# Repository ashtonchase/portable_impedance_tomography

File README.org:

* Portable Impedance Tomography System
This repository supports the UAH CPE 621 Advanced Embedded Systems project centered around the [[http://www.analog.com/media/en/technical-documentation/data-sheets/AD5933.pdf][Analog Devices AD5933 Impedance Analyzer]] for the use of impedance tomography.

** Overview

TBD

** Repository Structure

TBD

** Software 

Drivers are included for controlling the AD5933 module. Communication with the module is performed over I2C. The software drivers are device independent, so specific functions are to be used to map driver functionality to specific peripherals.

*** Porting Guide

A software porting guide is provided in [[./software/ad5933/hal/PORTING.org][PORTING GUIDLINE]]. 

** PCB Design 

A custom printed circuit board design is included. The design was developed in [[http://www.kicad.com][Kicad]].  The PCB project is available here [[https://github.com/ashtonchase/portable_impedance_tomography/tree/master/hardware/kicad_project][here]]. 

This PCB design in available via OSH Park. The project is located [[https://oshpark.com/shared_projects/npJ3mGp4][here]]

[[./hardware/kicad_project/output/top.png]]

[[./hardware/kicad_project/output/bottom.png]]

[[./hardware/kicad_project/output/3dtop.png]]

[[./hardware/kicad_project/output/3dbottom.png]]

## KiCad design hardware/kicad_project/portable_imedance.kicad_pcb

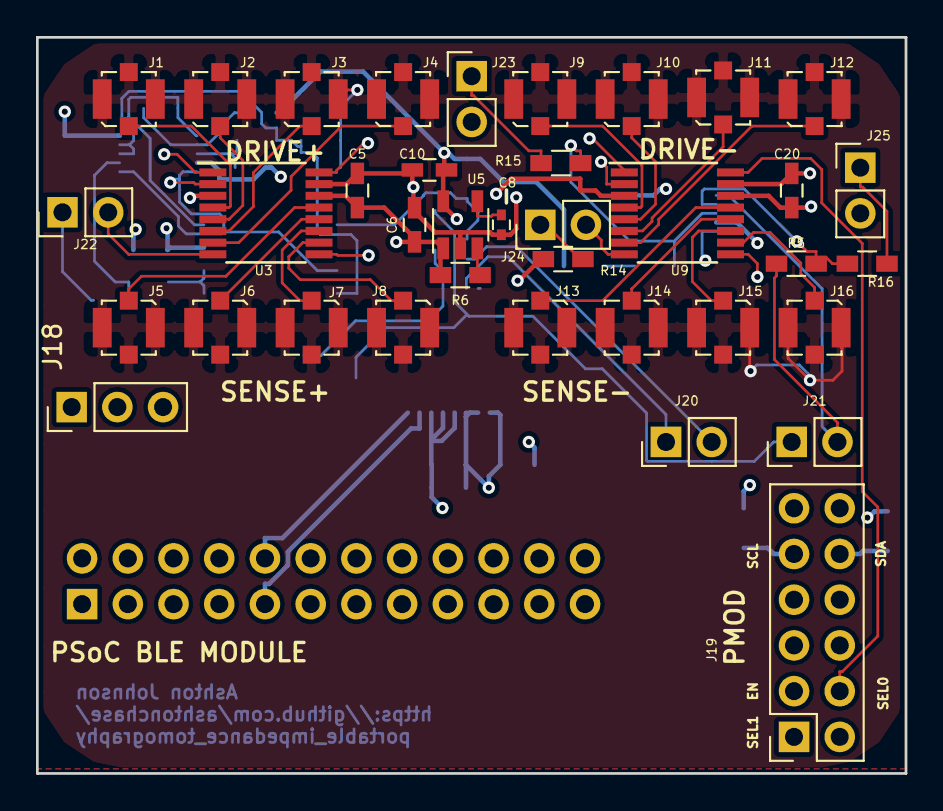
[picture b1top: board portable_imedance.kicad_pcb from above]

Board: 4 copper layers, 48.3 x 40.9 mm, 63 parts (0 on the bottom side), 51 nets.

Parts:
C1, C2: 0.1uF; C_0603_HandSoldering
C3: 10uF; C_0603_HandSoldering
C5, C20: 0.1u; C_0603_HandSoldering
C6, C10, C15, C16: 1u; C_0603_HandSoldering
C8: 10n; C_0402
C13: 33n; C_0402
C14, C18: 100n; C_0603_HandSoldering
J1, J2, J3, J4, J5, J6, J7, J8, J9, J10, J11, J12, J13, J14, J15, J16: UMC; Molex_Microcoaxial_RF
J17: Conn_02x12_Odd_Even; Socket_Strip_Straight_2x12_Pitch2.54mm
J18: Conn_01x03; Socket_Strip_Straight_1x03_Pitch2.54mm
J19: Conn_02x06_Odd_Even; Socket_Strip_Straight_2x06_Pitch2.54mm
J20, J21, J22, J23, J24, J25: Conn_01x02; Socket_Strip_Straight_1x02_Pitch2.54mm
R1, R2: 4.7k; R_0603_HandSoldering
R3, R5, R6, R10, R15, R16: 1k; R_0603_HandSoldering
R4, R13, R14, R17: 0; R_0603_HandSoldering
R7: 75k; R_0603_HandSoldering
R8, R9: 1M; R_0603_HandSoldering
R11: 75; R_0603_HandSoldering
R12: 10k; R_0603_HandSoldering
RV1: 20K; Potentiometer_Trimmer_Bourns_3214W
U2: AD5933; SSOP-16_5.3x6.2mm_Pitch0.65mm
U3, U9: ADG1209; TSSOP-16_4.4x5mm_Pitch0.65mm
U5: LD3985G25R_TSOT23; TSOT-23-5
U6, U7: OPA2836; TSSOP-10_3x3mm_Pitch0.5mm
U8: AD8130; SO-8_5.3x6.2mm_Pitch1.27mm

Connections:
+2V5: C10.1, R7.1, R9.1, R14.2, R17.2, U5.5
/AD5933 Front End/DRIVE_N: J24.1, R14.1
/AD5933 Front End/DRIVE_P: J22.1, R13.1
/AD5933 Front End/EN: J17.4, J19.3, U3.2, U6.5, U6.6, U7.5, U8.3, U9.2
/AD5933 Front End/SENSE_N: J25.1, R16.1
/AD5933 Front End/SENSE_P: J23.1, R15.1
/AD5933 Front End/SHIELD_DRIVE: J1.2, J2.2, J3.2, J4.2, J5.2, J6.2, J7.2, J8.2, J9.2, J10.2, J11.2, J12.2, J13.2, J14.2, J15.2, J16.2, R11.1, R12.2
/AD5933 Front End/VIN: J21.2, R5.2, U7.1
/AD5933 Front End/VOUT: C13.2, J20.2
/AD5933/AD5933_RFB: R4.2, RV1.3, U2.4
/AD5933/SCL: J17.10, J19.9, R2.2, U2.16
/AD5933/SDA: J17.9, J19.10, R1.2, U2.15
/AD5933/VIN: J21.1, R4.1, RV1.2, U2.5
/AD5933/VOUT: J20.1, U2.6
/Auxiliary Analog Connector/AIN: J17.22, J18.3
/Cypress BLE Headers/SEL0: J17.8, J19.4, U3.16, U9.16
/Cypress BLE Headers/SEL1: J17.6, J19.1, U3.1, U9.1
/Receive Mux/DRIVE: J22.2, U3.8
/Receive Mux/SA1: J1.1, U3.4
/Receive Mux/SA2: J2.1, U3.5
/Receive Mux/SA3: J3.1, U3.6
/Receive Mux/SA4: J4.1, U3.7
/Receive Mux/SENSE: J23.2, U3.9
/Transmit Mux/DRIVE: J24.2, U9.8
/Transmit Mux/SA1: J9.1, U9.4
/Transmit Mux/SA2: J10.1, U9.5
/Transmit Mux/SA3: J11.1, U9.6
/Transmit Mux/SA4: J12.1, U9.7
/Transmit Mux/SENSE: J25.2, U9.9
GND: C1.2, C2.2, C3.2, C5.2, C6.2, C8.2, C10.2, C14.2, C16.1, C18.2, C20.2, J17.1, J17.24, J18.1, J19.5, J19.11, R12.1, U2.12, U2.13, U2.14, U3.3, U3.15, U5.2, U6.4, U7.4, U8.2, U9.3, U9.15
unnamed: C8.1, U5.4
unnamed: C13.1, R7.2, U8.1
unnamed: C15.1, R9.2, U6.2
unnamed: C15.2, U6.1, U8.8
unnamed: C16.2, R8.2, U6.3
unnamed: J5.1, U3.13
unnamed: J6.1, U3.12
unnamed: J7.1, U3.11
unnamed: J8.1, U3.10
unnamed: J13.1, U9.13
unnamed: J14.1, U9.12
unnamed: J15.1, U9.11
unnamed: J16.1, U9.10
unnamed: R6.1, U5.3
unnamed: R10.1, R13.2, U6.7
unnamed: R10.2, U8.5, U8.6
unnamed: R8.1, R11.2, U6.8, U6.9, U8.4
unnamed: R3.1, R15.2, U7.3
unnamed: R5.1, R16.2, U7.2
unnamed: R3.2, R17.1
VCC: C1.1, C2.1, C3.1, C5.1, C6.1, C14.1, C18.1, C20.1, J17.2, J17.23, J18.2, J19.6, J19.12, R1.1, R2.1, R6.2, U2.9, U2.10, U2.11, U3.14, U5.1, U6.10, U7.10, U8.7, U9.14

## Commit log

2017-09-07 proposal and README
2017-09-07 added files for final report genereration using LaTeX.
2017-09-07 added PowerPoint Format to documentation.
2017-09-11 added kicad files
2017-10-12 added software files.
2017-10-13 added system states report
2017-10-14 added sofware files. added Doxyfile for generating documenation.
2017-10-14 added mid_term presentation (incomplete). added shell script to generate doxygen. added netlist.
2017-10-14 pcb design updates. updated README. updated mid_term presentation.
2017-10-14 added pictures of PCB.
2017-10-14 added PDF
2017-10-14 added mid_term.pdf
2017-10-14 added doxygen output reference manual
2017-10-18 update board to include additional connector
2017-10-18 updated board to include aux connector
2017-10-19 added kicad-library submodule to repository to prepare for handling library dependencies.
2017-10-19 Added BOM specific materials
2017-10-22 final project updates. BOM updates.
2017-11-17 document updates
2017-11-18 report updates
2017-11-28 added pictures
2017-11-28 added psoc project files. updated source code.
2017-11-28 added AD5933.pdf
2017-11-28 added final presentation.
2017-11-28 added final presentation
2017-11-28 updated final slides and psoc workspace.
2017-12-02 added debug_uart diagram.
2017-12-02 added more graphics pulled from mid-term slides into graphics folder.
2017-12-02 code indenting.
2017-12-02 updated psoc component APIs. had to update I2C functions as such to include timeouts. also the I2C Read Byte command changed.
2017-12-05 report updates.
